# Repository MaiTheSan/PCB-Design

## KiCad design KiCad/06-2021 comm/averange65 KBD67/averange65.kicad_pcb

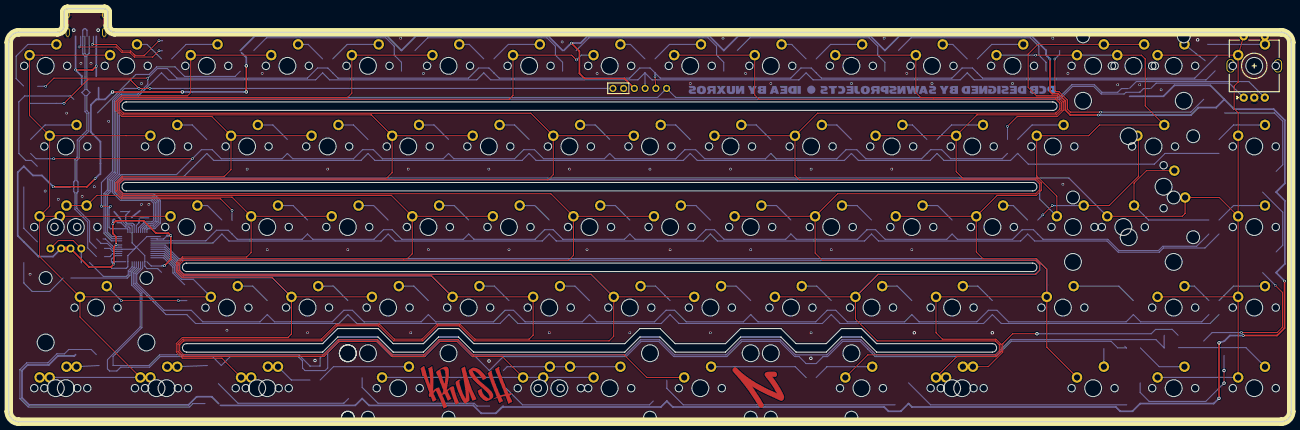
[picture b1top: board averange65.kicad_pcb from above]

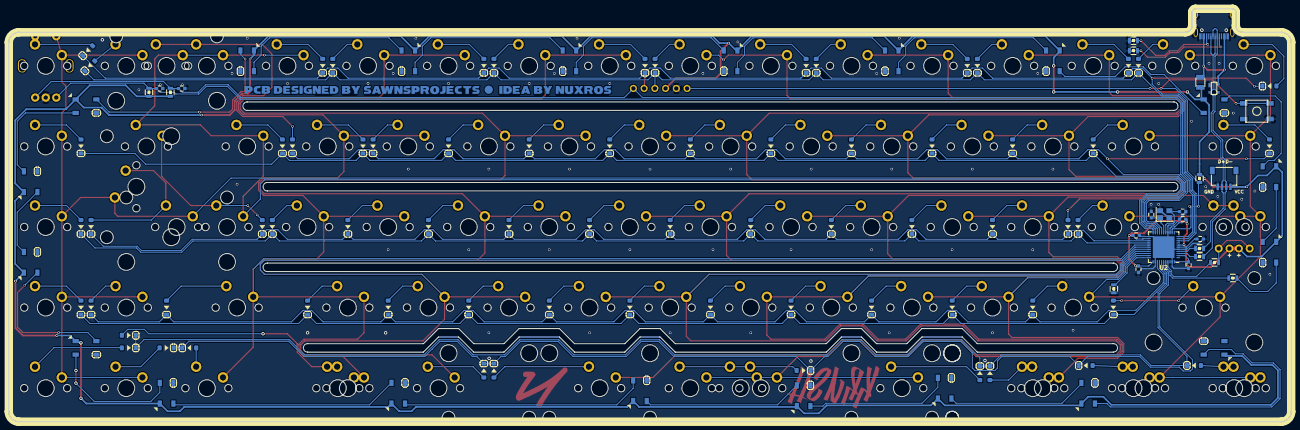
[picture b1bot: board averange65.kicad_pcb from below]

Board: 2 copper layers, 303.2 x 97.6 mm, 200 parts (116 on the bottom side), 127 nets.

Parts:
C1: 10uF; C_0603
C2, C3: 22pF; C_0603
C4, C5, C7, C8, C9: 0.1uF; C_0603
C6: 1uF; C_0603
D1, D2, D3, D4, D5, D6, D7, D8, D9, D10, D11, D12, D13, D14, D15, D16, D17, D18, D19, D20, D21, D22, D23, D24, D25, D26, D27, D28, D29, D30, D31, D32, D33, D34, D35, D36, D37, D38, D39, D40, D41, D42, D43, D45, D46, D47, D48, D49, D50, D51, D52, D53, D54, D55, D56, D57, D58, D59, D60, D61, D62, D63, D65, D66, D67, D70, D71, D72, D73, D74: D; D_SOD-123
D44: LED; MXOnly-LEDONLY-FLIPPED
D64: LED; MXOnly-LEDONLY
F1: Fuse; Fuse_SMD1206_Reflow
J1: Conn_01x04_Female; JST-SR-4
MX1, MX2, MX3, MX4, MX5, MX6, MX7, MX8, MX9, MX10, MX11, MX12, MX13, MX14, MX15, MX16, MX19, MX20, MX21, MX22, MX23, MX24, MX25, MX26, MX27, MX28, MX29, MX30, MX34, MX35, MX36, MX37, MX38, MX39, MX40, MX41, MX42, MX43, MX44, MX45, MX49, MX50, MX51, MX52, MX53, MX54, MX55, MX56, MX57, MX58, MX59, MX61, MX62, MX63, MX69, MX76, MX77, MX78: 1U; MXOnly-1U-NoLED
MX17: 2U; MXOnly-2U-NoLED
MX18, MX33, MX46, MX70, MX72: 1.5U; MXOnly-1.5U-NoLED
MX31: 1.25U-stepcap; MXOnly-1.25U-NoLED
MX32, MX60: 1.75U; MXOnly-1.75U-NoLED
MX47, MX48: 2.25U; MXOnly-2.25U-NoLED
MX64: ISO; MXOnly-ISO-ROTATED-ReversedStabilizers-NoLED
MX65, MX66, MX67, MX74, MX75, MX79: 1.25U; MXOnly-1.25U-NoLED
MX68: 6.25U; MXOnly-6.25U-ReversedStabilizers-NoLED
MX71: 6.25U; MXOnly-7U-ReversedStabilizers-NoLED
MX73: 2.25U; MXOnly-2.25U-ReversedStabilizers-NoLED
MX80: 2.75U; MXOnly-2.75U-ReversedStabilizers-NoLED
R1, R2: 5.1k; R_0805
R3, R4: 22; R_0805
R5, R9, R10: 10k; R_0805
R6: 1k; R_0805
R7, R8: 330R; R_0805
RGB1, RGB2, RGB3, RGB4, RGB5, RGB6, RGB7, RGB8, RGB9, RGB10, RGB11, RGB12, RGB13, RGB14, RGB15, RGB16, RGB17, RGB18, RGB19, RGB20: WS2812B; LED_WS2812B_PLCC4_5.0x5.0mm_P3.2mm
SW1: SW_Push; SKQG-1155865
SW2: Rotary_Encoder_Switch; RotaryEncoder_Alps_EC11E-Switch_Vertical_H20mm_Center
U1: PRTR5V0U2X; SOT143B
U2: ATmega32U4-MU; QFN-44-1EP_7x7mm_P0.5mm_EP5.15x5.15mm
U4: STF202-22T1G; Debug
USB1: HRO-TYPE-C-31-M-12; HRO-TYPE-C-31-M-12-Assembly
Y1: 16Mhz; Crystal_SMD_3225-4Pin_3.2x2.5mm

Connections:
+5V: C1.2, C4.2, C5.2, C7.2, D44.2, D64.2, F1.1, J1.1, R5.1, R9.2, R10.1, RGB1.1, RGB2.1, RGB3.1, RGB4.1, RGB5.1, RGB6.1, RGB7.1, RGB8.1, RGB9.1, RGB10.1, RGB11.1, RGB12.1, RGB13.1, RGB14.1, RGB15.1, RGB16.1, RGB17.1, RGB18.1, RGB19.1, RGB20.1, U2.2, U2.7, U2.14, U2.24, U2.34, U2.44, U4.4
CapLK: R8.2, U2.41
Col0: MX1.1, MX2.1, MX18.1, MX19.1, MX31.1, MX32.1, MX35.1, MX46.1, MX47.1, MX49.1, MX65.1, MX66.1, MX69.1, U2.32
Col1: MX3.1, MX4.1, MX20.1, MX21.1, MX36.1, MX37.1, MX51.1, MX52.1, MX67.1, MX70.1, U2.31
Col2: MX5.1, MX6.1, MX22.1, MX23.1, MX38.1, MX39.1, MX53.1, MX54.1, MX68.1, MX71.1, MX73.1, MX79.1, U2.30
Col3: MX7.1, MX8.1, MX24.1, MX25.1, MX40.1, MX41.1, MX55.1, MX56.1, MX80.1, U2.29
Col4: MX9.1, MX10.1, MX26.1, MX27.1, MX42.1, MX43.1, MX57.1, MX58.1, MX74.1, U2.28
Col5: MX11.1, MX12.1, MX28.1, MX29.1, MX44.1, MX45.1, MX59.1, MX60.1, MX72.1, MX75.1, MX76.1, U2.27
Col6: MX13.1, MX14.1, MX17.1, MX30.1, MX33.2, MX63.1, U2.22
Col7: MX15.1, MX16.1, MX34.1, MX48.1, MX50.1, MX61.1, MX62.1, MX64.2, MX77.1, MX78.1, SW2.S2, U2.21
D+: R3.1, U2.4
D-: R4.1, U2.3
DG+: J1.3, R3.2, U1.2, USB1.6, USB1.8
DG-: J1.2, R4.2, U1.3, USB1.5, USB1.7
EC-A: C9.2, R10.2, SW2.A, U2.18
EC-B: C8.1, R9.1, SW2.B, U2.11, U4.1
GND: C1.1, C2.2, C3.2, C4.1, C5.1, C6.2, C7.1, C8.2, C9.1, J1.4, R1.1, R2.1, R6.1, RGB1.3, RGB2.3, RGB3.3, RGB4.3, RGB5.3, RGB6.3, RGB7.3, RGB8.3, RGB9.3, RGB10.3, RGB11.3, RGB12.3, RGB13.3, RGB14.3, RGB15.3, RGB16.3, RGB17.3, RGB18.3, RGB19.3, RGB20.3, SW1.1, SW2.C, U1.1, U2.5, U2.15, U2.23, U2.35, U2.43, U2.45, U4.6, USB1.1, USB1.12, USB1.13, Y1.2, Y1.4
MOSI: D2.1, D4.1, D6.1, D8.1, D10.1, D12.1, D15.1, U2.10, U4.3
unnamed: C2.1, U2.17, Y1.1
unnamed: C3.1, U2.16, Y1.3
unnamed: C6.1, U2.6
unnamed: D1.2, MX1.2
unnamed: D2.2, MX2.2
unnamed: D3.2, MX3.2
unnamed: D4.2, MX4.2
unnamed: D5.2, MX5.2
unnamed: D6.2, MX6.2
unnamed: D7.2, MX7.2
unnamed: D8.2, MX8.2
unnamed: D9.2, MX9.2
unnamed: D10.2, MX10.2
unnamed: D11.2, MX11.2
unnamed: D12.2, MX12.2
unnamed: D13.2, MX13.2
unnamed: D14.2, MX14.2, MX17.2
unnamed: D15.2, MX15.2
unnamed: D16.2, MX16.2
unnamed: D17.2, MX18.2
unnamed: D18.2, MX19.2
unnamed: D19.2, MX20.2
unnamed: D20.2, MX21.2
unnamed: D21.2, MX22.2
unnamed: D22.2, MX23.2
unnamed: D23.2, MX24.2
unnamed: D24.2, MX25.2
unnamed: D25.2, MX26.2
unnamed: D26.2, MX27.2
unnamed: D27.2, MX28.2
unnamed: D28.2, MX29.2
unnamed: D29.2, MX30.2
unnamed: D30.2, MX31.2, MX32.2
unnamed: D31.2, MX33.1, MX63.2
unnamed: D32.2, MX34.2
unnamed: D33.2, MX35.2
unnamed: D34.2, MX36.2
unnamed: D35.2, MX37.2
unnamed: D36.2, MX38.2
unnamed: D37.2, MX39.2
unnamed: D38.2, MX40.2
unnamed: D39.2, MX41.2
unnamed: D40.2, MX42.2
unnamed: D41.2, MX43.2
unnamed: D42.2, MX44.2
unnamed: D43.2, MX45.2
unnamed: D44.1, D64.1, R8.1
unnamed: D45.2, MX48.2, MX64.1
unnamed: D46.2, MX47.2
unnamed: D47.2, MX50.2
unnamed: D48.2, MX49.2
unnamed: D49.2, MX51.2
unnamed: D50.2, MX52.2
unnamed: D51.2, MX53.2
unnamed: D52.2, MX54.2
unnamed: D53.2, MX55.2
unnamed: D54.2, MX56.2
unnamed: D55.2, MX57.2
unnamed: D56.2, MX58.2
unnamed: D57.2, MX59.2
unnamed: D58.2, MX60.2
unnamed: D59.2, MX61.2
unnamed: D60.2, MX62.2
unnamed: D61.2, MX46.2, MX65.2
unnamed: D62.2, MX66.2, MX69.2
unnamed: D63.2, MX67.2, MX70.2
unnamed: D65.2, MX68.2, MX71.2, MX79.2
unnamed: D66.2, MX73.2
unnamed: D67.2, MX80.2
unnamed: D70.2, MX74.2
unnamed: D71.2, MX72.2, MX75.2
unnamed: D72.2, MX76.2
unnamed: D73.2, MX77.2
unnamed: D74.2, MX78.2
unnamed: R1.2, USB1.10
unnamed: R2.2, USB1.4
unnamed: R6.2, U2.33
unnamed: R7.2, U2.40
unnamed: RGB1.2, RGB2.4
unnamed: RGB1.4, RGB11.2
unnamed: RGB2.2, RGB3.4
unnamed: RGB3.2, RGB4.4
unnamed: RGB4.2, RGB5.4
unnamed: RGB5.2, RGB6.4
unnamed: RGB6.2, RGB7.4
unnamed: RGB7.2, RGB8.4
unnamed: RGB8.2, RGB9.4
unnamed: RGB10.2, RGB20.4
unnamed: RGB9.2, RGB10.4
unnamed: RGB11.4, RGB12.2
unnamed: RGB13.4, RGB14.2
unnamed: RGB14.4, RGB15.2
unnamed: RGB15.4, RGB16.2
unnamed: RGB16.4, RGB17.2
unnamed: RGB17.4, RGB18.2
unnamed: RGB18.4, RGB19.2
unnamed: RGB19.4, RGB20.2
RGBLED: R7.1, RGB12.4
RST: R5.2, SW1.2, U2.13, U4.5
Row0: D1.1, D3.1, D5.1, D7.1, D9.1, D11.1, D13.1, D16.1, U2.9, U4.2
Row2: D14.1, D17.1, D19.1, D21.1, D23.1, D25.1, D27.1, U2.19
Row3: D18.1, D20.1, D22.1, D24.1, D26.1, D28.1, D29.1, D32.1, U2.20
Row4: D30.1, D31.1, D34.1, D36.1, D38.1, D40.1, D42.1, D45.1, U2.25
Row5: D33.1, D35.1, D37.1, D39.1, D41.1, D43.1, D47.1, U2.26
Row6: D46.1, D49.1, D51.1, D53.1, D55.1, D57.1, D60.1, U2.37
Row7: D48.1, D50.1, D52.1, D54.1, D56.1, D58.1, D59.1, U2.36
Row8: D61.1, D63.1, D66.1, D71.1, D74.1, U2.38
Row9: D62.1, D65.1, D67.1, D70.1, D72.1, D73.1, U2.39
VCC: F1.2, U1.4, USB1.2, USB1.11

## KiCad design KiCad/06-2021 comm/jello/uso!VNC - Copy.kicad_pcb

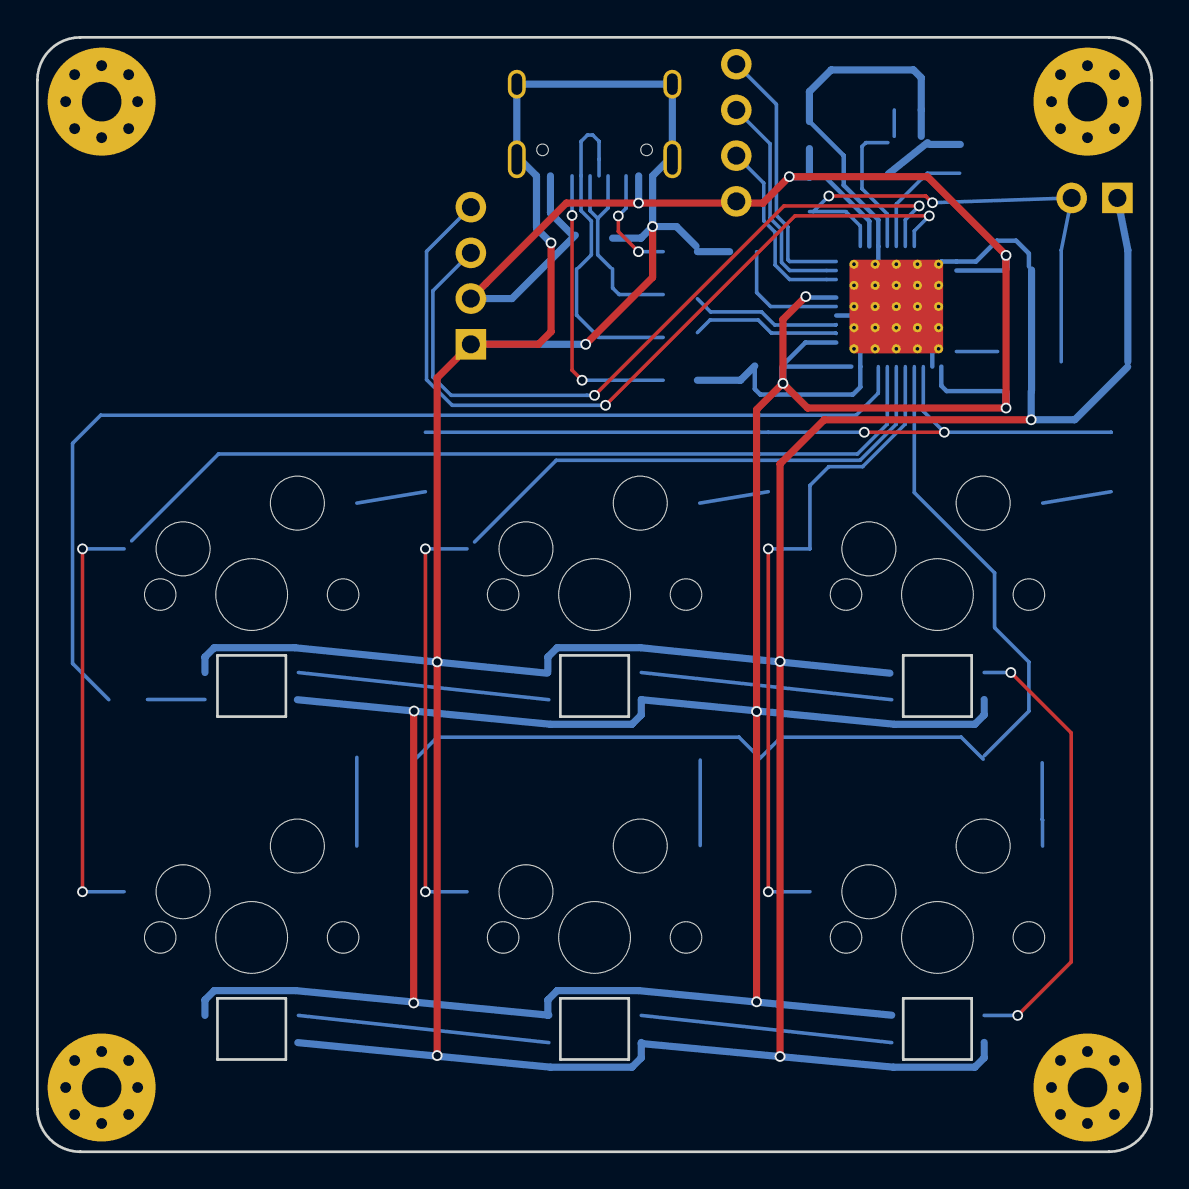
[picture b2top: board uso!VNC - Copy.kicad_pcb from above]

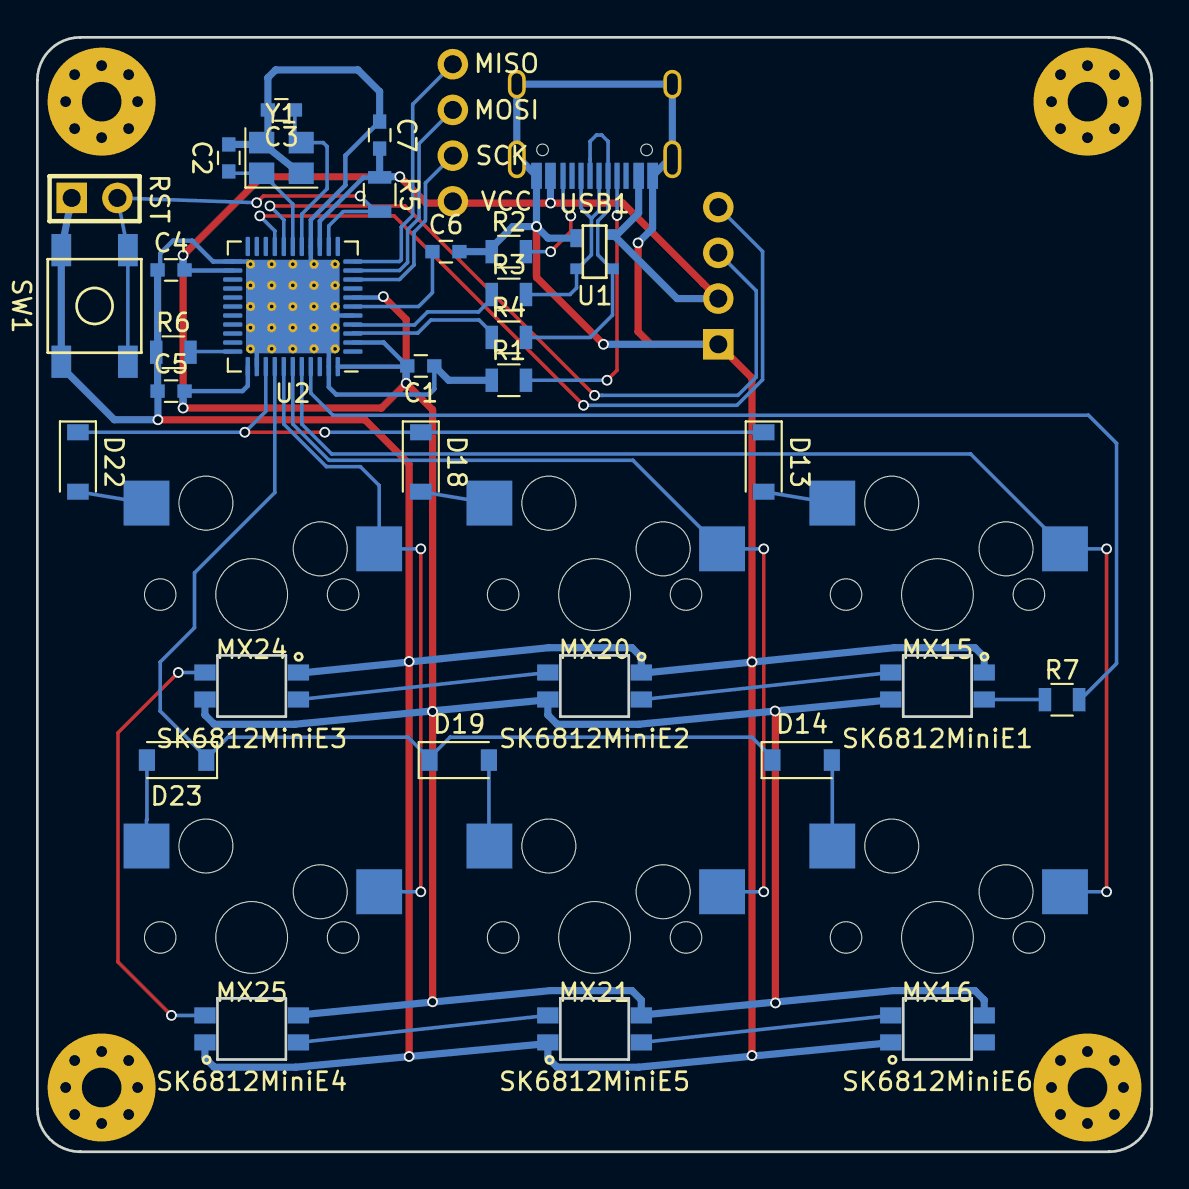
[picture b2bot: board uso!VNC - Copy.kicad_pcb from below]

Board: 2 copper layers, 61.9 x 61.9 mm, 44 parts (34 on the bottom side), 36 nets.

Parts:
C1: 10uF; C_0603
C2, C3: 22pF; C_0603
C4, C5, C7: 0.1uF; C_0603
C6: 1uF; C_0603
D13, D14, D18, D19, D22, D23: D; D_SOD-123
LOGO2, LOGO3, LOGO4, LOGO5: Logo_Open_Hardware_Large; mounting-circular
MX15, MX16, MX20, MX21, MX24, MX25: MX-NoLED; MXOnly-1U-Hotswap
R1, R2: 5.1k; R_0805
R3, R4: 22; R_0805
R5: 10k; R_0805
R6: 1k; R_0805
R7: R; R_0805
SK6812MiniE1, SK6812MiniE2, SK6812MiniE3: WS2812B; RGB-6028_FLIPPED
SK6812MiniE4, SK6812MiniE5, SK6812MiniE6: WS2812B; RGB-6028
SW1: SW_Push; SKQG-1155865
U1: PRTR5V0U2X; SOT143B
U2: ATmega32U4-MU; QFN-44-1EP_7x7mm_P0.5mm_EP5.2x5.2mm_ThermalVias
U3: STF202-22T1G; 0.91_SSD1306_OLED
U4, U5: STF202-22T1G; Reset_Pretty
USB1: HRO-TYPE-C-31-M-12; HRO-TYPE-C-31-M-12-Assembly
Y1: 16Mhz; Crystal_SMD_3225-4Pin_3.2x2.5mm

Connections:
+5V: C1.2, C4.2, C5.2, C7.2, R5.1, SK6812MiniE1.1, SK6812MiniE2.1, SK6812MiniE3.1, SK6812MiniE4.1, SK6812MiniE5.1, SK6812MiniE6.1, U1.4, U2.2, U2.7, U2.14, U2.24, U2.34, U2.44, U3.2, U4.4, USB1.2, USB1.11
COL0: MX15.1, MX16.1, U2.40
COL1: MX20.1, MX21.1, U2.39
COL2: MX24.1, MX25.1, U2.38
D+: R3.1, U2.4
D-: R4.1, U2.3
GND: C1.1, C2.2, C3.2, C4.1, C5.1, C6.2, C7.1, R1.1, R2.1, R6.1, SK6812MiniE1.3, SK6812MiniE2.3, SK6812MiniE3.3, SK6812MiniE4.3, SK6812MiniE5.3, SK6812MiniE6.3, SW1.1, U1.1, U2.5, U2.15, U2.23, U2.35, U2.43, U2.45, U3.1, U5.6, USB1.1, USB1.12, USB1.13, Y1.2, Y1.4
MISO: U2.11, U4.1
MOSI: U2.10, U4.3
unnamed: C2.1, U2.17, Y1.1
unnamed: C3.1, U2.16, Y1.3
unnamed: C6.1, U2.6
unnamed: D13.2, MX15.2
unnamed: D14.2, MX16.2
unnamed: D18.2, MX20.2
unnamed: D19.2, MX21.2
unnamed: D22.2, MX24.2
unnamed: D23.2, MX25.2
unnamed: R1.2, USB1.4
unnamed: R2.2, USB1.10
unnamed: R3.2, U1.2, USB1.6, USB1.8
unnamed: R4.2, U1.3, USB1.5, USB1.7
unnamed: R6.2, U2.33
unnamed: R7.2, U2.41
unnamed: SK6812MiniE1.2, SK6812MiniE2.4
unnamed: SK6812MiniE2.2, SK6812MiniE3.4
unnamed: SK6812MiniE3.2, SK6812MiniE4.4
unnamed: SK6812MiniE4.2, SK6812MiniE5.4
unnamed: SK6812MiniE5.2, SK6812MiniE6.4
RGBLED: R7.1, SK6812MiniE1.4
ROW0: D13.1, D18.1, D22.1, U2.36
ROW1: D14.1, D19.1, D23.1, U2.37
RST: R5.2, SW1.2, U2.13, U5.5
SCK: U2.9, U4.2
SCL: U2.18, U3.3
SDA: U2.19, U3.4

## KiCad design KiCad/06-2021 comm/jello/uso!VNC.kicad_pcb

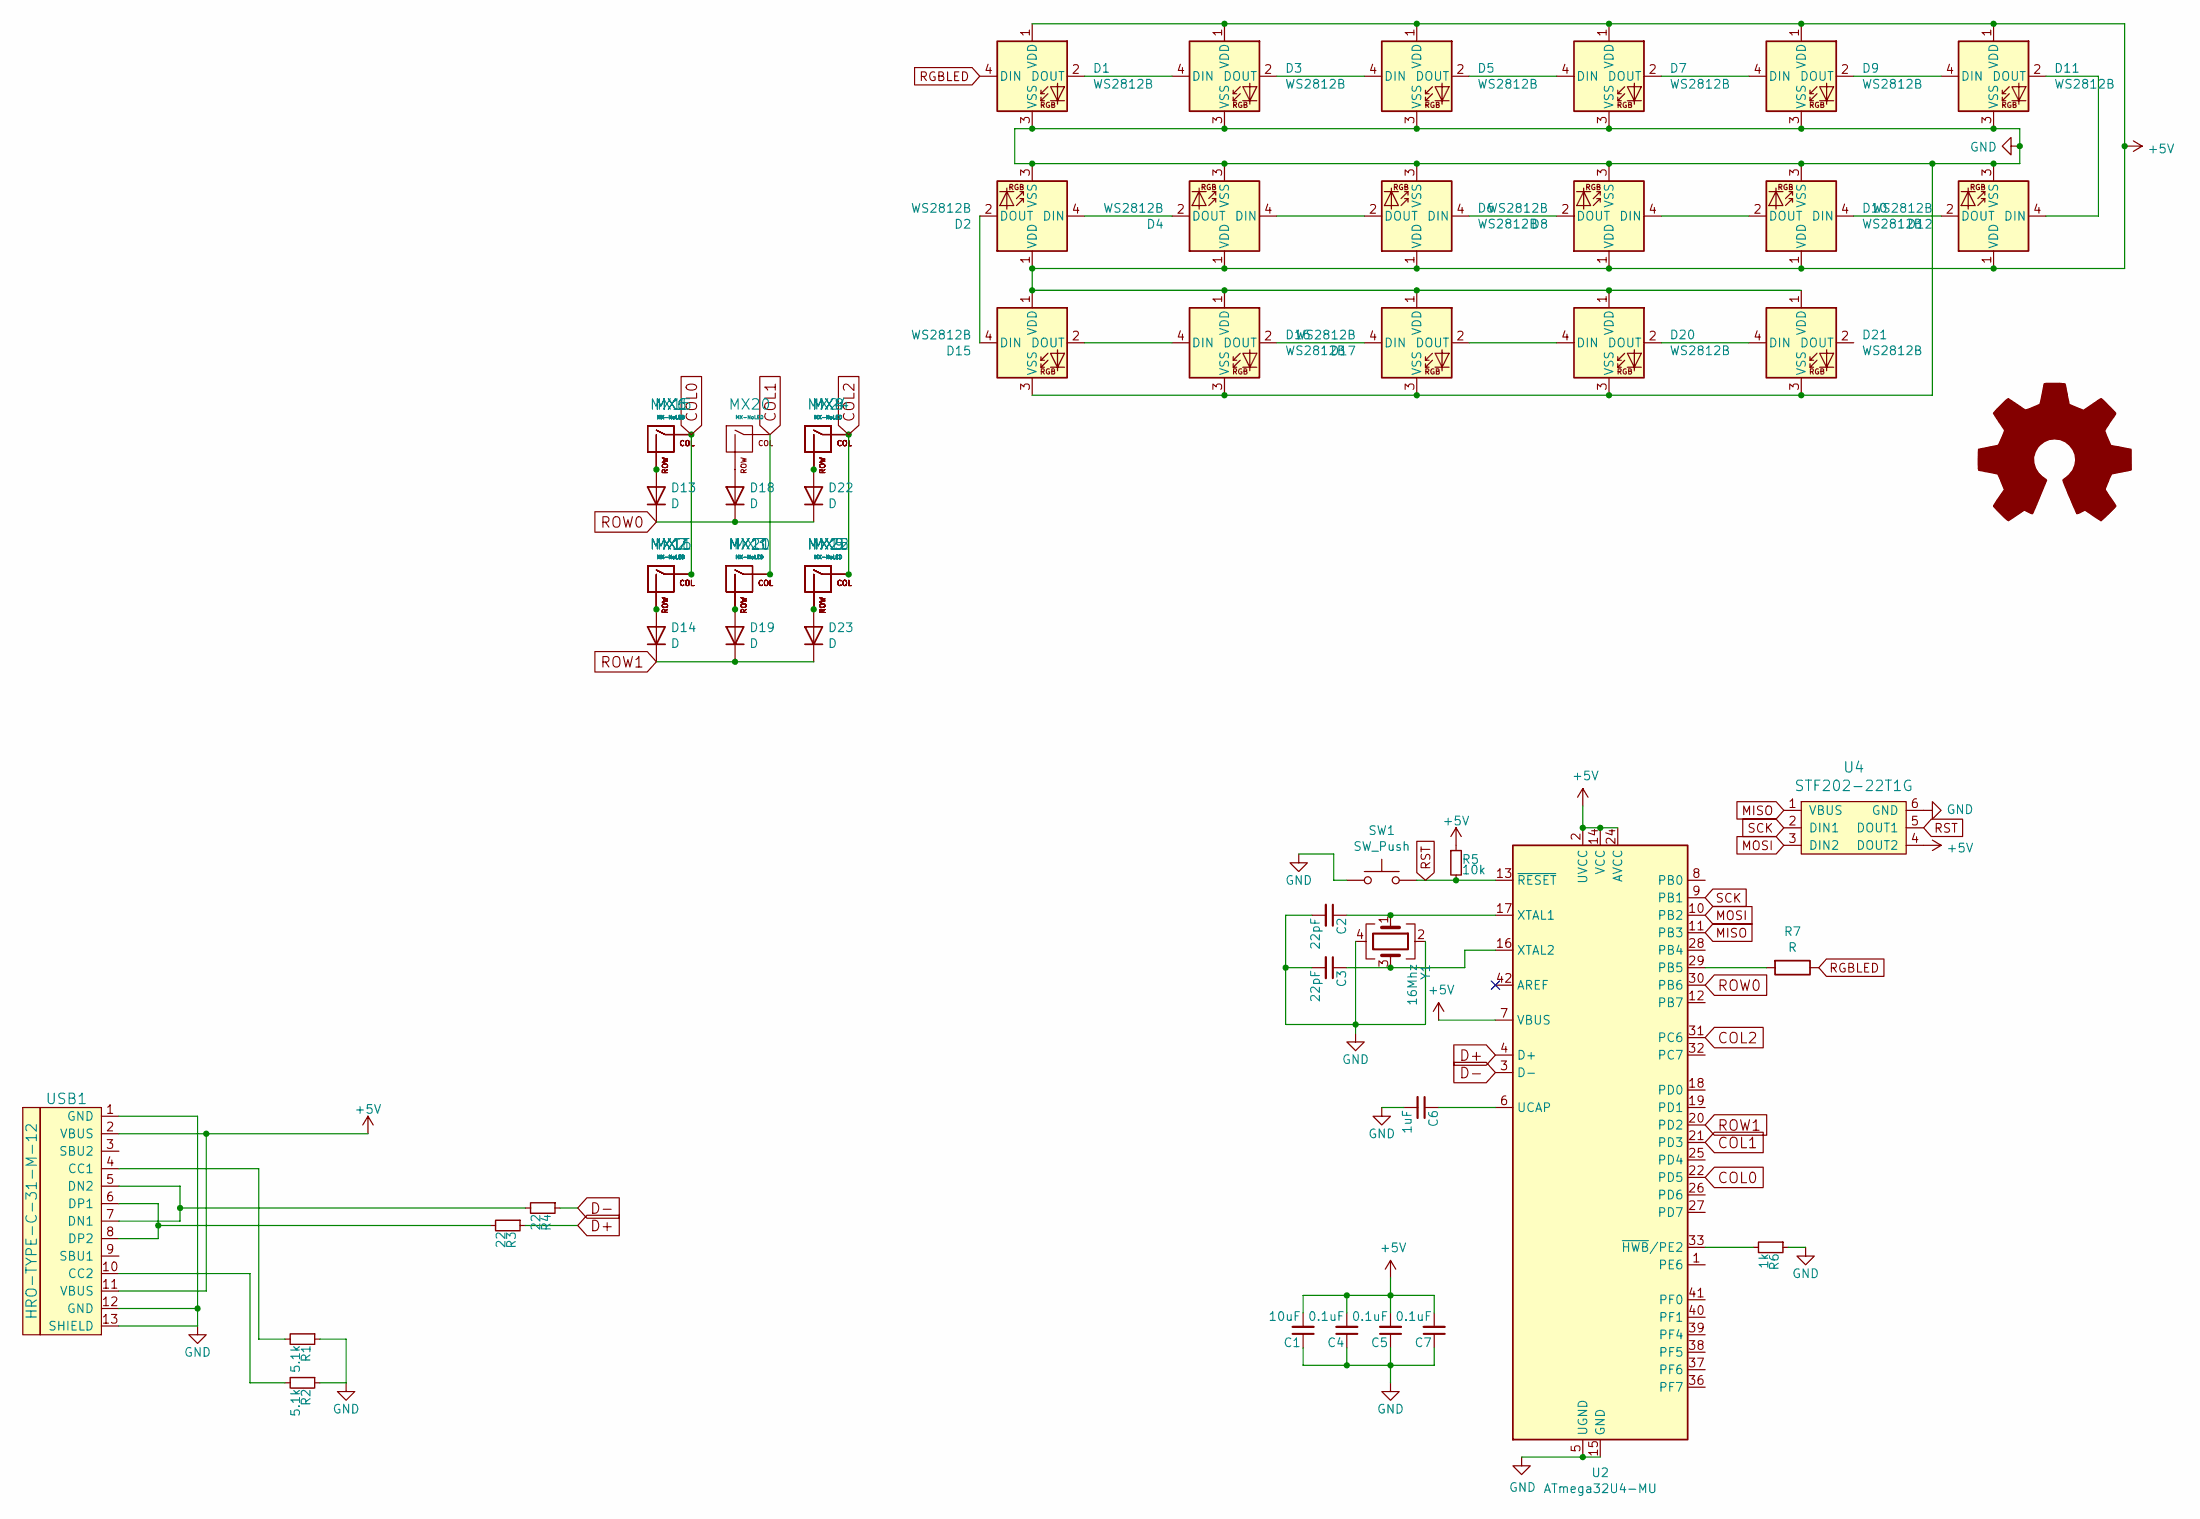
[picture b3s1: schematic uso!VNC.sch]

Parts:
C1: 10uF; C_0603
C2, C3: 22pF; C_0603
C4, C5, C7: 0.1uF; C_0603
C6: 1uF; C_0603
D1, D3, D5, D7, D9: WS2812B; RGB-6028
D2, D4, D8, D11, D12, D16, D20, D21: WS2812B; RGB-6028_FLIPPED
D6, D10, D15, D17: WS2812B; RGB-6028-mid
D13, D14, D18, D19, D22, D23: D; D_SOD-123
LOGO1: Logo_Open_Hardware_Large; sanpjxlogo
MX1, MX4, MX6, MX8, MX15, MX20, MX24: MX-NoLED; MXOnly-1U-NoLED
MX2, MX5, MX7, MX9, MX16, MX25: MX-NoLED; MXOnly-1.25U-NoLED
MX3: MX-NoLED; MXOnly-6.25U-ReversedStabilizers-NoLED
MX10: MX-NoLED; MXOnly-6.5U-ReversedStabilizers-NoLED
MX11, MX12: MX-NoLED; MXOnly-1.5U-NoLED
MX21: MX-NoLED; MXOnly-7U-ReversedStabilizers-NoLED
R1, R2: 5.1k; R_0805
R3, R4: 22; R_0805
R5: 10k; R_0805
R6: 1k; R_0805
R7: R; R_0805
SW1: SW_Push; SKQG-1155865
U2: ATmega32U4-MU; QFN-44-1EP_7x7mm_P0.5mm_EP5.15x5.15mm
U4: STF202-22T1G; Reset_Pretty
USB1: HRO-TYPE-C-31-M-12; HRO-TYPE-C-31-M-12-Assembly
Y1: 16Mhz; Crystal_SMD_3225-4Pin_3.2x2.5mm

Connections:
+5V: C1.2, C4.2, C5.2, C7.2, D1.1 (VDD), D2.1 (VDD), D3.1 (VDD), D4.1 (VDD), D5.1 (VDD), D6.1 (VDD), D7.1 (VDD), D8.1 (VDD), D9.1 (VDD), D10.1 (VDD), D11.1 (VDD), D12.1 (VDD), D15.1 (VDD), D16.1 (VDD), D17.1 (VDD), D20.1 (VDD), D21.1 (VDD), R5.1, U2.2 (UVCC), U2.7 (VBUS), U2.14 (VCC), U2.24 (AVCC), U2.34 (VCC), U2.44 (AVCC), U4.4 (DOUT2), USB1.2 (VBUS), USB1.11 (VBUS)
COL0: MX1.1 (COL), MX2.1 (COL), MX6.1 (COL), MX7.1 (COL), MX11.1 (COL), MX15.1 (COL), MX16.1 (COL), U2.22 (PD5)
COL1: MX3.1 (COL), MX10.1 (COL), MX20.1 (COL), MX21.1 (COL), U2.21 (PD3)
COL2: MX4.1 (COL), MX5.1 (COL), MX8.1 (COL), MX9.1 (COL), MX12.1 (COL), MX24.1 (COL), MX25.1 (COL), U2.31 (PC6)
D+: R3.1, U2.4 (D+)
D-: R4.1, U2.3 (D-)
GND: C1.1, C2.2, C3.2, C4.1, C5.1, C6.2, C7.1, D1.3 (VSS), D2.3 (VSS), D3.3 (VSS), D4.3 (VSS), D5.3 (VSS), D6.3 (VSS), D7.3 (VSS), D8.3 (VSS), D9.3 (VSS), D10.3 (VSS), D11.3 (VSS), D12.3 (VSS), D15.3 (VSS), D16.3 (VSS), D17.3 (VSS), D20.3 (VSS), D21.3 (VSS), R1.1, R2.1, R6.1, SW1.1, U2.5 (UGND), U2.15 (GND), U2.23 (GND), U2.35 (GND), U2.43 (GND), U2.45 (GND), U4.6 (GND), USB1.1 (GND), USB1.12 (GND), USB1.13 (SHIELD), Y1.2, Y1.4
MISO: U2.11 (PB3), U4.1 (VBUS)
MOSI: U2.10 (PB2), U4.3 (DIN2)
unnamed: C2.1, U2.17 (XTAL1), Y1.1
unnamed: C3.1, U2.16 (XTAL2), Y1.3
unnamed: C6.1, U2.6 (UCAP)
unnamed: D1.2 (DOUT), D3.4 (DIN)
unnamed: D2.4 (DIN), D4.2 (DOUT)
unnamed: D3.2 (DOUT), D5.4 (DIN)
unnamed: D4.4 (DIN), D6.2 (DOUT)
unnamed: D5.2 (DOUT), D7.4 (DIN)
unnamed: D6.4 (DIN), D8.2 (DOUT)
unnamed: D7.2 (DOUT), D9.4 (DIN)
unnamed: D8.4 (DIN), D10.2 (DOUT)
unnamed: D10.4 (DIN), D12.2 (DOUT)
unnamed: D11.2 (DOUT), D12.4 (DIN)
unnamed: D9.2 (DOUT), D11.4 (DIN)
unnamed: D13.2 (A), MX1.2 (ROW), MX6.2 (ROW), MX15.2 (ROW)
unnamed: D14.2 (A), MX2.2 (ROW), MX7.2 (ROW), MX11.2 (ROW), MX16.2 (ROW)
unnamed: D15.2 (DOUT), D16.4 (DIN)
unnamed: D2.2 (DOUT), D15.4 (DIN)
unnamed: D16.2 (DOUT), D17.4 (DIN)
unnamed: D17.2 (DOUT), D20.4 (DIN)
unnamed: D18.2 (A), MX20.2 (ROW)
unnamed: D19.2 (A), MX3.2 (ROW), MX10.2 (ROW), MX21.2 (ROW)
unnamed: D20.2 (DOUT), D21.4 (DIN)
unnamed: D22.2 (A), MX4.2 (ROW), MX8.2 (ROW), MX24.2 (ROW)
unnamed: D23.2 (A), MX5.2 (ROW), MX9.2 (ROW), MX12.2 (ROW), MX25.2 (ROW)
unnamed: R1.2, USB1.4 (CC1)
unnamed: R2.2, USB1.10 (CC2)
unnamed: R3.2, USB1.6 (DP1), USB1.8 (DP2)
unnamed: R4.2, USB1.5 (DN2), USB1.7 (DN1)
unnamed: R6.2, U2.33 (~HWB~/PE2)
unnamed: R7.2, U2.29 (PB5)
RGBLED: D1.4 (DIN), R7.1
ROW0: D13.1 (K), D18.1 (K), D22.1 (K), U2.30 (PB6)
ROW1: D14.1 (K), D19.1 (K), D23.1 (K), U2.20 (PD2)
RST: R5.2, SW1.2, U2.13 (~RESET), U4.5 (DOUT1)
SCK: U2.9 (PB1), U4.2 (DIN1)

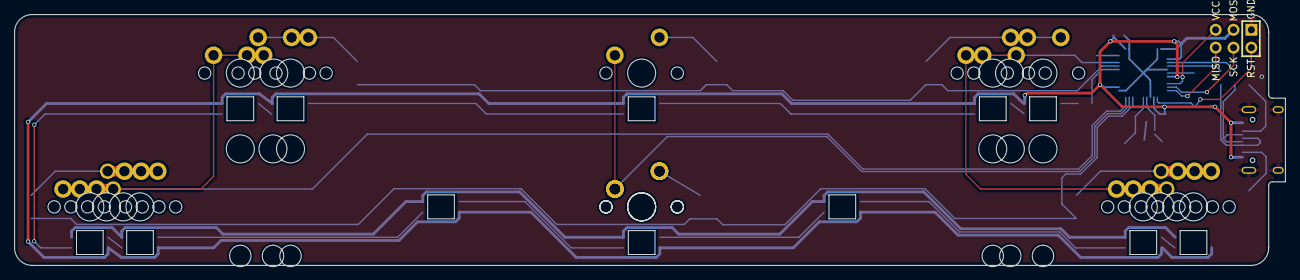
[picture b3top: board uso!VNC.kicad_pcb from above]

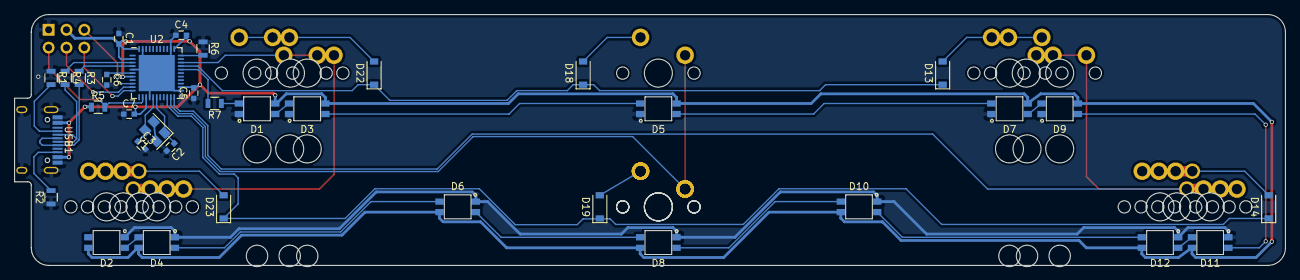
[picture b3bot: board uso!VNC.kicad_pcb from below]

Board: 2 copper layers, 181.0 x 35.7 mm, 55 parts (35 on the bottom side), 40 nets.

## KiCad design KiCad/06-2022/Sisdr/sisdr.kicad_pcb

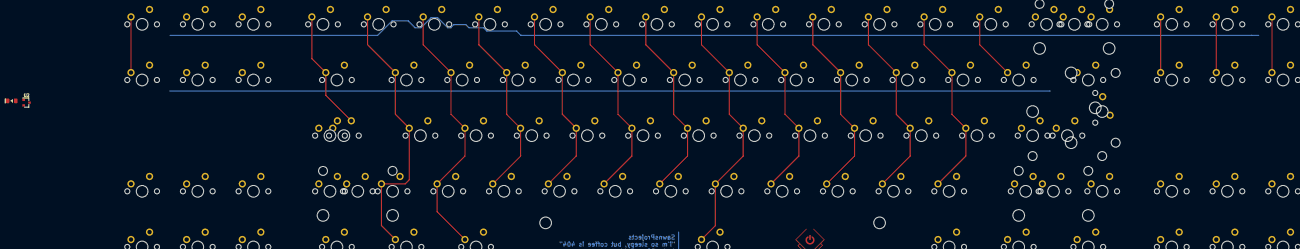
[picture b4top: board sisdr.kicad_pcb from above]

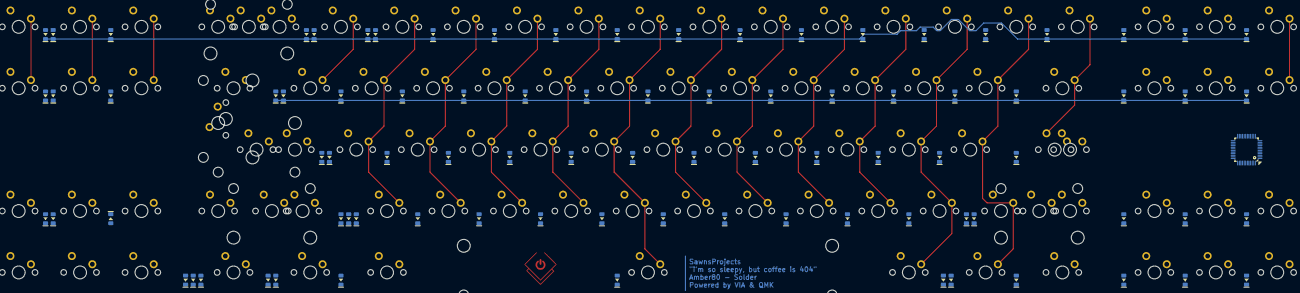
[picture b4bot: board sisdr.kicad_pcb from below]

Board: 2 copper layers, 183 parts (88 on the bottom side), 116 nets.

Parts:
D1, D2, D3, D4, D5, D6, D7, D8, D9, D10, D11, D12, D13, D14, D15, D16, D17, D18, D19, D20, D21, D22, D23, D24, D25, D26, D27, D28, D29, D30, D31, D32, D33, D34, D35, D36, D37, D38, D39, D40, D41, D42, D43, D44, D45, D46, D47, D48, D49, D50, D51, D52, D53, D54, D55, D56, D57, D58, D59, D60, D61, D62, D63, D64, D65, D66, D67, D68, D69, D70, D71, D72, D73, D74, D75, D76, D77, D78, D79, D80, D81, D83, D84, D85, D86, D88, D89, D90: D; DIODE_1206_SawnsProjects
MX1, MX2, MX9, MX10, MX11, MX12, MX13, MX14, MX15, MX16, MX17, MX18, MX19, MX21, MX22, MX23, MX24, MX25, MX26, MX27, MX28, MX29, MX30, MX31, MX32, MX33, MX34, MX35, MX36, MX37, MX38, MX39, MX40, MX41, MX42, MX43, MX44, MX45, MX47, MX48, MX49, MX50, MX51, MX52, MX53, MX54, MX55, MX56, MX57, MX58, MX59, MX60, MX61, MX62, MX63, MX64, MX65, MX66, MX67, MX68, MX69, MX73, MX74, MX76, MX78, MX79, MX82, MX85, MX86, MX87, MX89, MX90, MX91, MX92, MX94, MX95, MX96: 1U; MXOnly-1U-NoLED
MX3, MX7, MX20, MX72, MX80, MX83: 1.5U; MXOnly-1.5U-NoLED
MX4, MX5: 1.25U; MXOnly-1.25U-NoLED
MX6: 2.25U; MXOnly-2.25U-NoLED
MX8, MX70: 1.75U; MXOnly-1.75U-NoLED
MX46: 7U; MXOnly-7U-ReversedStabilizers-NoLED
MX71: 2.75U; MXOnly-2.75U-NoLED
MX75: 2U; MXOnly-2U-NoLED
MX77: 2.25U; MXOnly-2.25U-ReversedStabilizers-NoLED
MX81: ISO; MXOnly-ISO-ROTATED-ReversedStabilizers-NoLED
U1: STM32F072CBTx; LQFP-48_7x7mm_P0.5mm
U2: MCP1700-2502E_SOT23; SOT-23

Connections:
+3V3: D78.2, U1.1, U1.9, U1.24, U1.36, U1.48, U2.2
+5V: D78.1, U2.3
C0: MX15.1, MX21.1, MX26.1, MX31.1
C1: MX36.1, MX41.1, MX47.1, MX52.1
C2: MX57.1, MX62.1, MX67.1, MX73.1
C3: MX2.1, MX3.1, MX4.1, MX5.1, MX6.1, MX7.1, MX8.2
C4: MX10.1, MX11.1, MX12.1, MX13.1, MX14.1
C5: MX16.1, MX17.1, MX18.1, MX19.1, MX20.1
C6: MX22.1, MX23.1, MX24.1, MX25.1
C7: MX27.1, MX28.1, MX29.1, MX30.1
C8: MX32.1, MX33.1, MX34.1, MX35.1
C9: MX37.1, MX38.1, MX39.1, MX40.1
C10: MX42.1, MX43.1, MX44.1, MX45.1, MX46.1
C11: MX48.1, MX49.1, MX50.1, MX51.1
C12: MX53.1, MX54.1, MX55.1, MX56.1
C13: MX58.1, MX59.1, MX60.1, MX61.1
C14: MX63.1, MX64.1, MX65.1, MX66.1
C15: MX68.1, MX69.1, MX70.1, MX71.1, MX72.1
C16: MX74.1, MX75.1, MX76.1, MX77.1, MX78.1, MX79.1, MX80.2, MX81.2
C17: MX82.1, MX83.1
C18: MX1.1, MX85.1, MX86.1, MX87.1
C19: MX89.1, MX90.1, MX91.1, MX92.1
C20: MX9.1, MX94.1, MX95.1, MX96.1
GND: U1.8, U1.23, U1.35, U1.47
unnamed: D1.2, MX1.2
unnamed: D2.2, MX2.2
unnamed: D3.2, MX3.2
unnamed: D4.2, MX4.2, MX8.1
unnamed: D5.2, MX5.2, MX6.2
unnamed: D6.2, MX7.2
unnamed: D7.2, MX9.2
unnamed: D8.2, MX10.2
unnamed: D9.2, MX11.2
unnamed: D10.2, MX12.2
unnamed: D11.2, MX13.2
unnamed: D12.2, MX14.2
unnamed: D13.2, MX15.2
unnamed: D14.2, MX16.2
unnamed: D15.2, MX17.2
unnamed: D16.2, MX18.2
unnamed: D17.2, MX19.2
unnamed: D18.2, MX20.2
unnamed: D19.2, MX21.2
unnamed: D20.2, MX22.2
unnamed: D21.2, MX23.2
unnamed: D22.2, MX24.2
unnamed: D23.2, MX25.2
unnamed: D24.2, MX26.2
unnamed: D25.2, MX27.2
unnamed: D26.2, MX28.2
unnamed: D27.2, MX29.2
unnamed: D28.2, MX30.2
unnamed: D29.2, MX31.2
unnamed: D30.2, MX32.2
unnamed: D31.2, MX33.2
unnamed: D32.2, MX34.2
unnamed: D33.2, MX35.2
unnamed: D34.2, MX36.2
unnamed: D35.2, MX37.2
unnamed: D36.2, MX38.2
unnamed: D37.2, MX39.2
unnamed: D38.2, MX40.2
unnamed: D39.2, MX41.2
unnamed: D40.2, MX42.2
unnamed: D41.2, MX43.2
unnamed: D42.2, MX44.2
unnamed: D43.2, MX45.2
unnamed: D44.2, MX46.2
unnamed: D45.2, MX47.2
unnamed: D46.2, MX48.2
unnamed: D47.2, MX49.2
unnamed: D48.2, MX50.2
unnamed: D49.2, MX51.2
unnamed: D50.2, MX52.2
unnamed: D51.2, MX53.2
unnamed: D52.2, MX54.2
unnamed: D53.2, MX55.2
unnamed: D54.2, MX56.2
unnamed: D55.2, MX57.2
unnamed: D56.2, MX58.2
unnamed: D57.2, MX59.2
unnamed: D58.2, MX60.2
unnamed: D59.2, MX61.2
unnamed: D60.2, MX62.2
unnamed: D61.2, MX63.2
unnamed: D62.2, MX64.2
unnamed: D63.2, MX65.2
unnamed: D64.2, MX66.2
unnamed: D65.2, MX67.2
unnamed: D66.2, MX68.2
unnamed: D67.2, MX69.2
unnamed: D68.2, MX70.2, MX71.2
unnamed: D69.2, MX72.2
unnamed: D70.2, MX73.2
unnamed: D71.2, MX74.2, MX75.2
unnamed: D72.2, MX76.2, MX80.1
unnamed: D73.2, MX77.2, MX81.1
unnamed: D74.2, MX78.2
unnamed: D75.2, MX79.2
unnamed: D76.2, MX82.2
unnamed: D77.2, MX83.2
unnamed: D79.2, MX85.2
unnamed: D80.2, MX86.2
unnamed: D81.2, MX87.2
unnamed: D83.2, MX89.2
unnamed: D84.2, MX90.2
unnamed: D85.2, MX91.2
unnamed: D86.2, MX92.2
unnamed: D88.2, MX94.2
unnamed: D89.2, MX95.2
unnamed: D90.2, MX96.2
R0: D2.1, D8.1, D13.1, D14.1, D20.1, D25.1, D30.1, D34.1, D35.1, D40.1, D46.1, D51.1, D55.1, D56.1, D61.1, D66.1, D71.1, D76.1, D79.1, D83.1, D88.1
R1: D3.1, D9.1, D15.1, D19.1, D21.1, D26.1, D31.1, D36.1, D39.1, D41.1, D47.1, D52.1, D57.1, D60.1, D62.1, D67.1, D72.1, D80.1, D84.1, D89.1
R2: D4.1, D10.1, D16.1, D22.1, D27.1, D32.1, D37.1, D42.1, D48.1, D53.1, D58.1, D63.1, D73.1
R3: D1.1, D5.1, D7.1, D11.1, D17.1, D23.1, D24.1, D28.1, D33.1, D38.1, D43.1, D45.1, D49.1, D54.1, D59.1, D64.1, D65.1, D68.1, D74.1, D85.1
R4: D6.1, D12.1, D18.1, D29.1, D44.1, D50.1, D69.1, D70.1, D75.1, D77.1, D81.1, D86.1, D90.1
